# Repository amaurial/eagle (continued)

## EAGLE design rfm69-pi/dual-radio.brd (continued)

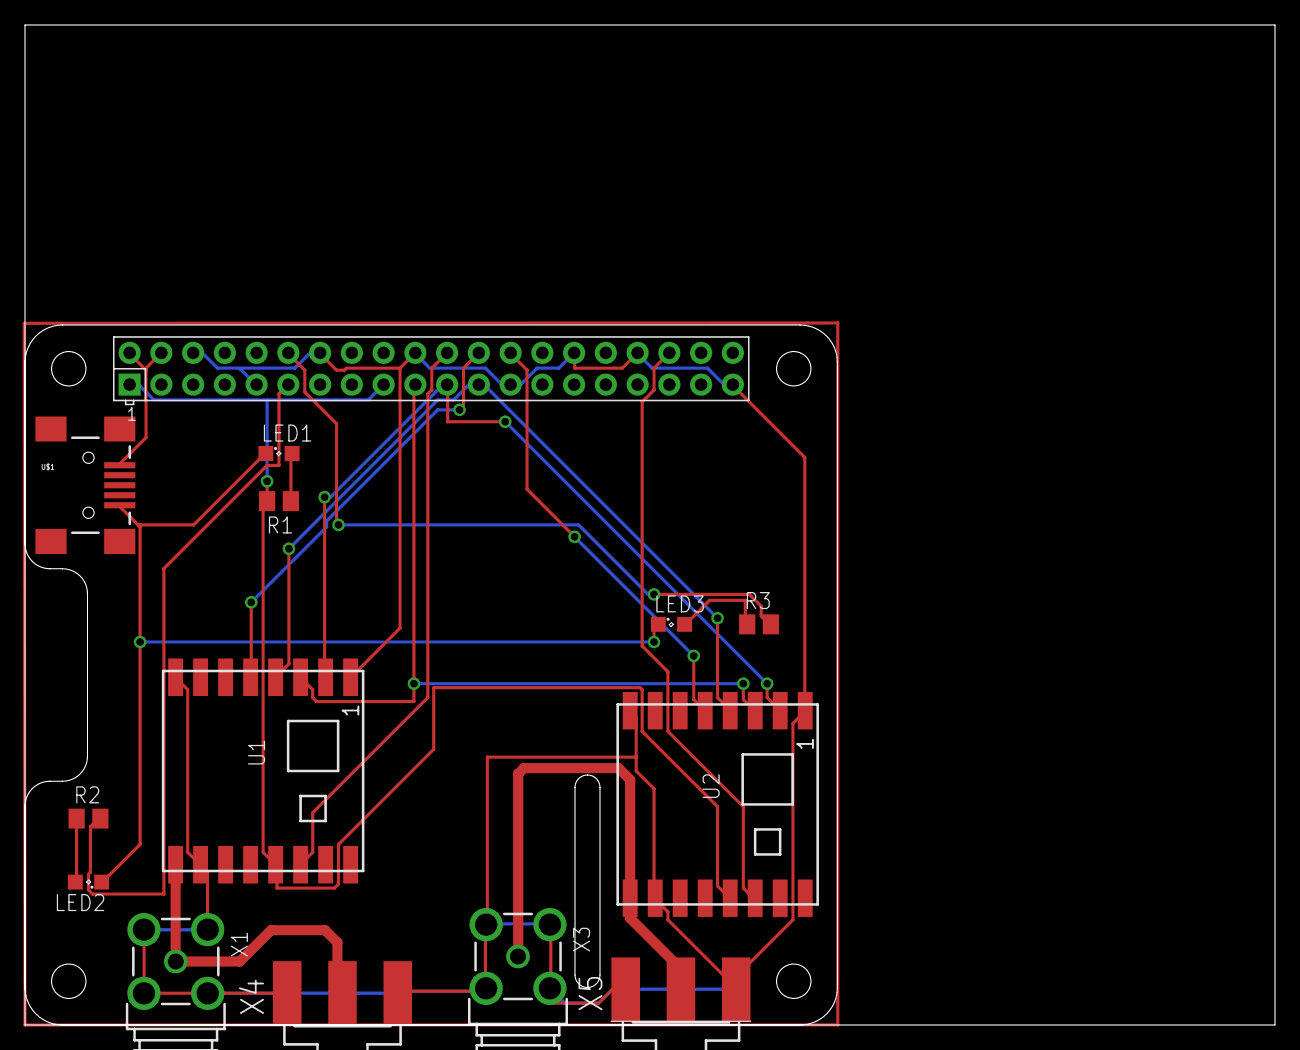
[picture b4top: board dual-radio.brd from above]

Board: 2 copper layers, 100.0 x 80.0 mm, 14 parts (0 on the bottom side), 18 nets.

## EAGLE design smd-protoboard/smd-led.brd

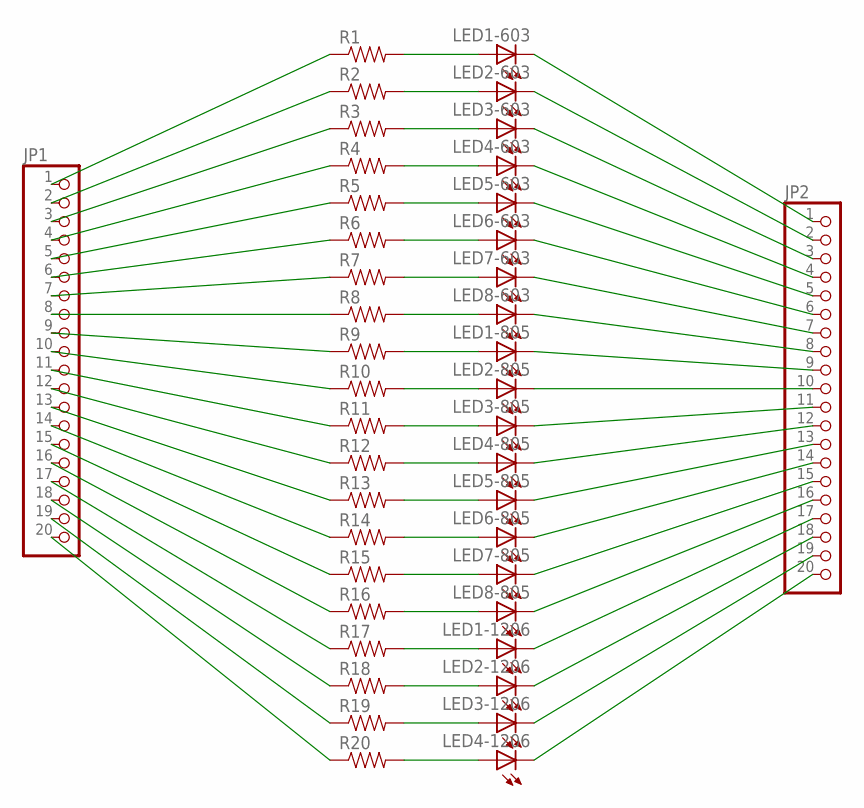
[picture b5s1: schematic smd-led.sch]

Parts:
JP1, JP2: PINHD-1X20; 1X20
LED1-603, LED2-603, LED3-603, LED4-603, LED5-603, LED6-603, LED7-603, LED8-603: LEDSML0603; SML0603
LED1-805, LED2-805, LED3-805, LED4-805, LED5-805, LED6-805, LED7-805, LED8-805: LEDSML0805; SML0805
LED1-1206, LED2-1206, LED3-1206, LED4-1206: LEDSML1206; SML1206
R1, R2, R3, R4, R5, R6, R7, R8, R9, R10, R11, R12, R13, R14, R15, R16, R17, R18, R19, R20: RESISTOR0805-RES; 0805

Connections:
unnamed: JP1.1, R1.1
unnamed: JP1.2, R2.1
unnamed: JP1.3, R3.1
unnamed: JP1.4, R4.1
unnamed: JP1.5, R5.1
unnamed: JP1.6, R6.1
unnamed: JP1.7, R7.1
unnamed: JP1.8, R8.1
unnamed: JP1.9, R9.1
unnamed: JP1.10, R10.1
unnamed: JP1.11, R11.1
unnamed: JP1.12, R12.1
unnamed: JP1.13, R13.1
unnamed: JP1.14, R14.1
unnamed: JP1.15, R15.1
unnamed: JP1.16, R16.1
unnamed: JP1.17, R17.1
unnamed: JP1.18, R18.1
unnamed: JP1.19, R19.1
unnamed: JP1.20, R20.1
unnamed: LED1-603.A, R1.2
unnamed: LED2-603.A, R2.2
unnamed: LED3-603.A, R3.2
unnamed: LED4-603.A, R4.2
unnamed: LED5-603.A, R5.2
unnamed: LED6-603.A, R6.2
unnamed: LED7-603.A, R7.2
unnamed: LED8-603.A, R8.2
unnamed: LED1-805.A, R9.2
unnamed: LED2-805.A, R10.2
unnamed: LED3-805.A, R11.2
unnamed: LED4-805.A, R12.2
unnamed: LED5-805.A, R13.2
unnamed: LED6-805.A, R14.2
unnamed: LED7-805.A, R15.2
unnamed: LED8-805.A, R16.2
unnamed: LED1-1206.A, R17.2
unnamed: LED2-1206.A, R18.2
unnamed: LED3-1206.A, R19.2
unnamed: LED4-1206.A, R20.2
unnamed: JP2.1, LED1-603.C
unnamed: JP2.2, LED2-603.C
unnamed: JP2.3, LED3-603.C
unnamed: JP2.4, LED4-603.C
unnamed: JP2.5, LED5-603.C
unnamed: JP2.6, LED6-603.C
unnamed: JP2.7, LED7-603.C
unnamed: JP2.8, LED8-603.C
unnamed: JP2.9, LED1-805.C
unnamed: JP2.10, LED2-805.C
unnamed: JP2.11, LED3-805.C
unnamed: JP2.12, LED4-805.C
unnamed: JP2.13, LED5-805.C
unnamed: JP2.14, LED6-805.C
unnamed: JP2.15, LED7-805.C
unnamed: JP2.16, LED8-805.C
unnamed: JP2.17, LED1-1206.C
unnamed: JP2.18, LED2-1206.C
unnamed: JP2.19, LED3-1206.C
unnamed: JP2.20, LED4-1206.C

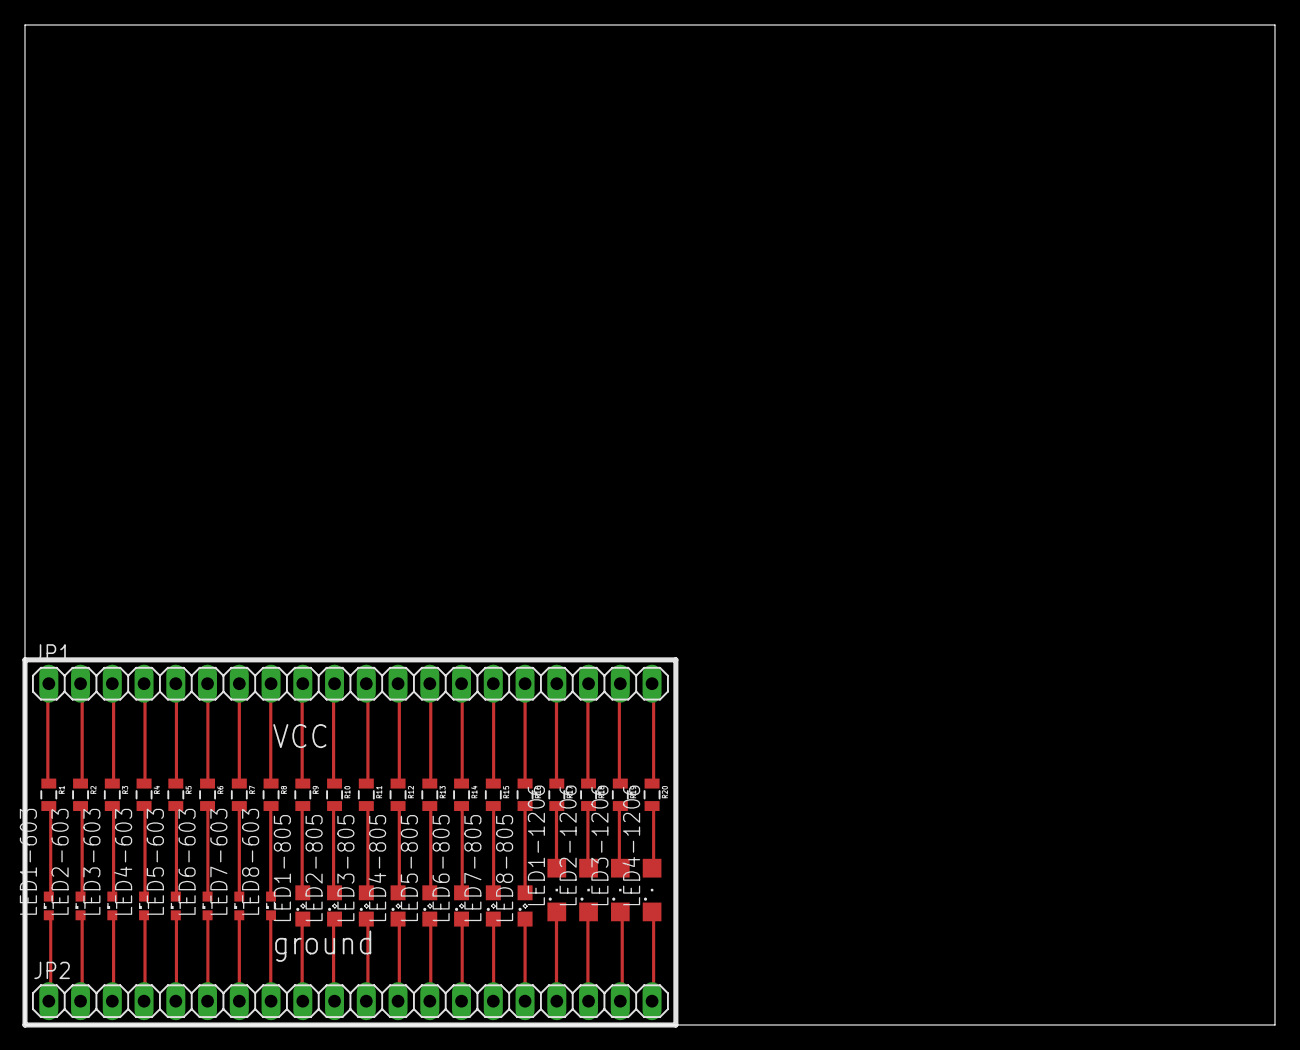
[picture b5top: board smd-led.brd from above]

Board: 2 copper layers, 100.0 x 80.0 mm, 42 parts (0 on the bottom side), 60 nets.

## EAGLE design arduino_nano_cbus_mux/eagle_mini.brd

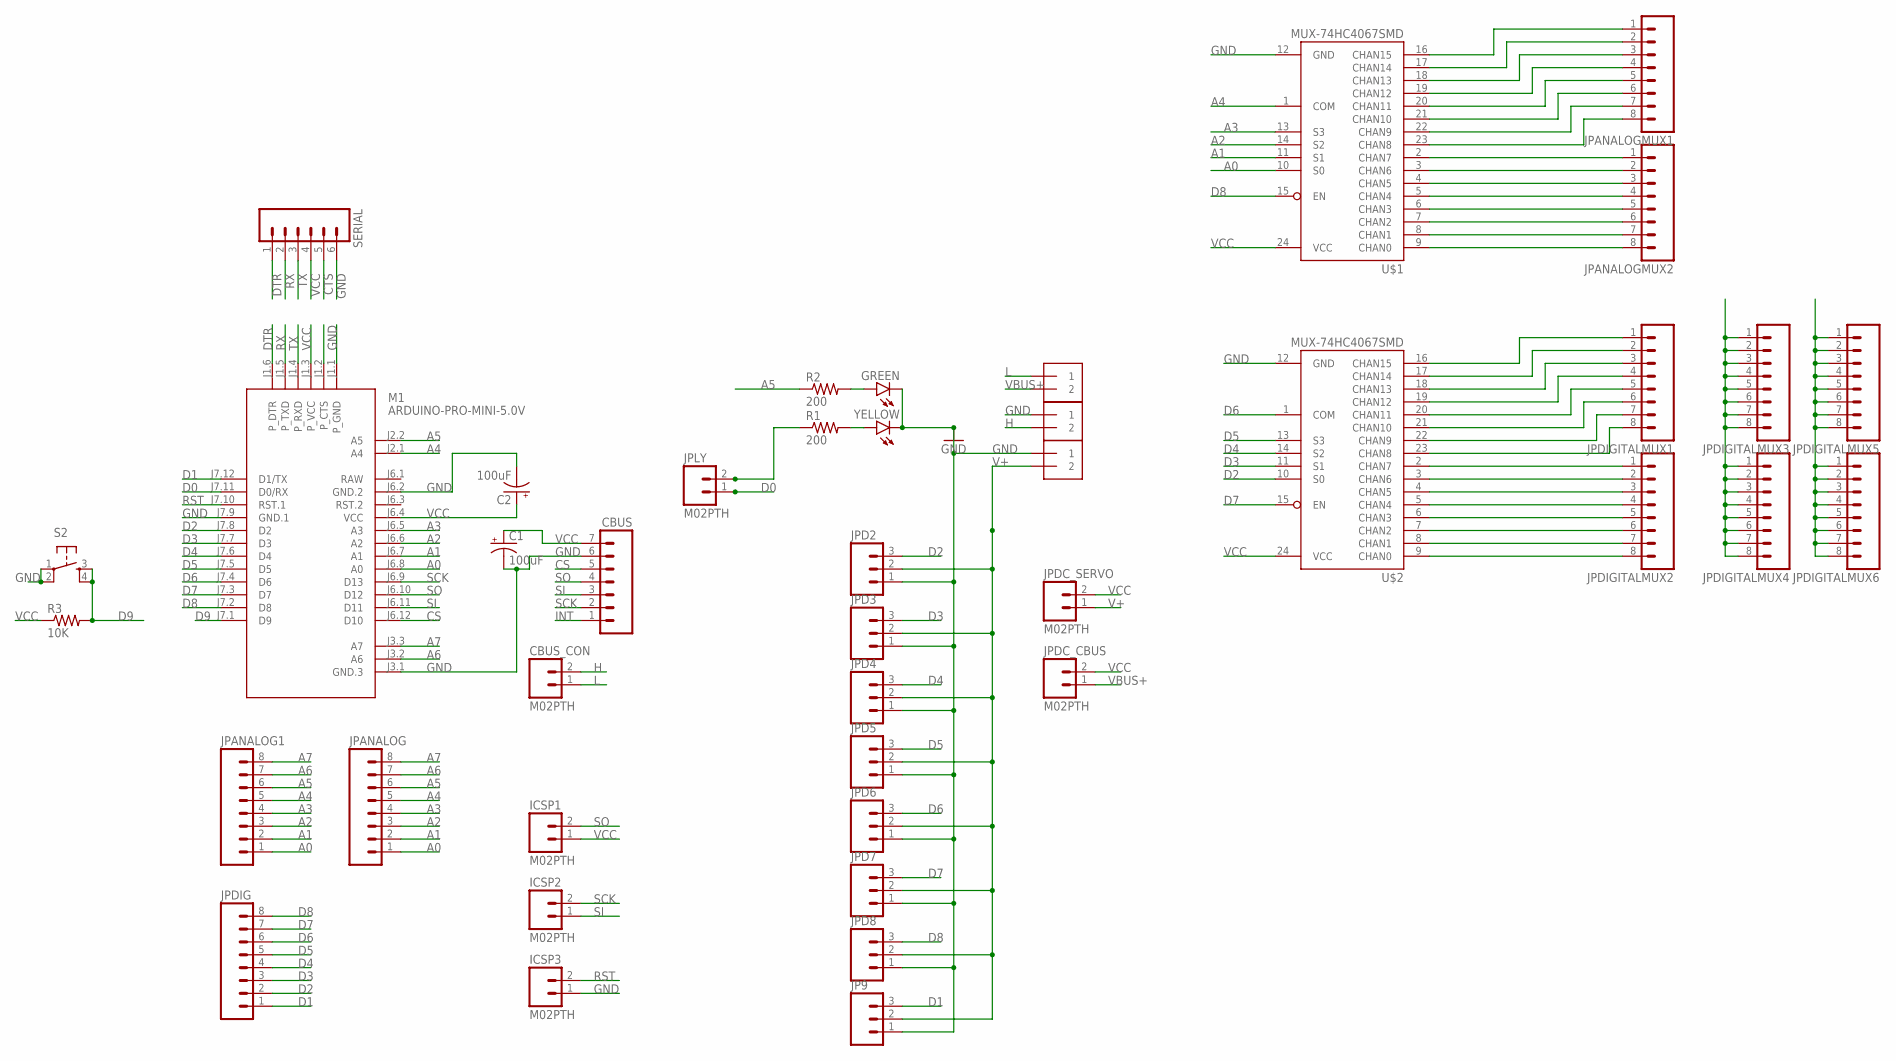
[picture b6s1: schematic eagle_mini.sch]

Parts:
C1, C2: 100uF; E2,5-6
CBUS: M07; 1X07
CBUS_CON: M02PTH; 1X02
EXT_VCC: 1X2-3.5MM
GREEN: LED-3MM-NO_SILK; LED3MM-NS
ICSP1, ICSP2, ICSP3: M02PTH; 1X02
J1, J2: 1X2-3.5MM
JP9: M03PTH; 1X03
JPANALOG, JPANALOG1: M08; 1X08_ROUND
JPANALOGMUX1, JPANALOGMUX2: M08; 1X08_ROUND
JPD2, JPD3, JPD4, JPD5, JPD6, JPD7, JPD8: M03PTH; 1X03
JPDC_CBUS: M02PTH; 1X02
JPDC_SERVO: M02PTH; 1X02
JPDIG: M08; 1X08_ROUND
JPDIGITALMUX1, JPDIGITALMUX2, JPDIGITALMUX3, JPDIGITALMUX4, JPDIGITALMUX5, JPDIGITALMUX6: M08; 1X08_ROUND
JPLY: M02PTH; 1X02
M1: ARDUINO-PRO-MINI-5.0V; ARDUINO-PRO-MINI
R1, R2: 200; AXIAL-0.3
R3: 10K; AXIAL-0.3
S2: TAC_SWITCHPTH; TACTILE-PTH
SERIAL: M06SILK_FEMALE_PTH; 1X06
U$1, U$2: MUX-74HC4067SMD; SSOP24
YELLOW: LED-3MM-NO_SILK; LED3MM-NS

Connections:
6: JPDIGITALMUX2.2, U$2.3 (CHAN6)
A0: JPANALOG.1, JPANALOG1.1, M1.J6.8 (A0), U$1.10 (S0)
A1: JPANALOG.2, JPANALOG1.2, M1.J6.7 (A1), U$1.11 (S1)
A2: JPANALOG.3, JPANALOG1.3, M1.J6.6 (A2), U$1.14 (S2)
A3: JPANALOG.4, JPANALOG1.4, M1.J6.5 (A3), U$1.13 (S3)
A4: JPANALOG.5, JPANALOG1.5, M1.J2.1 (A4), U$1.1 (COM)
A5: JPANALOG.6, JPANALOG1.6, M1.J2.2 (A5), R2.P$1 (1)
A6: JPANALOG.7, JPANALOG1.7, M1.J3.2 (A6)
A7: JPANALOG.8, JPANALOG1.8, M1.J3.3 (A7)
CS: CBUS.5, M1.J6.12 (D10)
CTS: SERIAL.5
D0: JPLY.1, M1.J7.11 (D0/RX)
D1: JP9.3, JPDIG.1, M1.J7.12 (D1/TX)
D2: JPD2.3, JPDIG.2, M1.J7.8 (D2), U$2.10 (S0)
D3: JPD3.3, JPDIG.3, M1.J7.7 (D3), U$2.11 (S1)
D4: JPD4.3, JPDIG.4, M1.J7.6 (D4), U$2.14 (S2)
D5: JPD5.3, JPDIG.5, M1.J7.5 (D5), U$2.13 (S3)
D6: JPD6.3, JPDIG.6, M1.J7.4 (D6), U$2.1 (COM)
D7: JPD7.3, JPDIG.7, M1.J7.3 (D7), U$2.15 (EN)
D8: JPD8.3, JPDIG.8, M1.J7.2 (D8), U$1.15 (EN)
D9: M1.J7.1 (D9), R3.P$2 (2), S2.3, S2.4
DTR: M1.J1.6 (P_DTR), SERIAL.1
GND: C1.-, C2.-, CBUS.6, EXT_VCC.1, GREEN.K (C), ICSP3.1, J1.1, JP9.1, JPD2.1, JPD3.1, JPD4.1, JPD5.1, JPD6.1, JPD7.1, JPD8.1, JPDIGITALMUX3.1, JPDIGITALMUX3.2, JPDIGITALMUX3.3, JPDIGITALMUX3.4, JPDIGITALMUX3.5, JPDIGITALMUX3.6, JPDIGITALMUX3.7, JPDIGITALMUX3.8, JPDIGITALMUX4.1, JPDIGITALMUX4.2, JPDIGITALMUX4.3, JPDIGITALMUX4.4, JPDIGITALMUX4.5, JPDIGITALMUX4.6, JPDIGITALMUX4.7, JPDIGITALMUX4.8, M1.J1.1 (P_GND), M1.J3.1 (GND.3), M1.J6.2 (GND.2), M1.J7.9 (GND.1), S2.1, S2.2, SERIAL.6, U$1.12 (GND), U$2.12 (GND), YELLOW.K (C)
H: CBUS_CON.2, J1.2
INT: CBUS.1
L: CBUS_CON.1, J2.1
MA0: JPANALOGMUX2.8, U$1.9 (CHAN0)
MA1: JPANALOGMUX2.7, U$1.8 (CHAN1)
MA2: JPANALOGMUX2.6, U$1.7 (CHAN2)
MA3: JPANALOGMUX2.5, U$1.6 (CHAN3)
MA4: JPANALOGMUX2.4, U$1.5 (CHAN4)
MA5: JPANALOGMUX2.3, U$1.4 (CHAN5)
MA6: JPANALOGMUX2.2, U$1.3 (CHAN6)
MA7: JPANALOGMUX2.1, U$1.2 (CHAN7)
MA8: JPANALOGMUX1.8, U$1.23 (CHAN8)
MA9: JPANALOGMUX1.7, U$1.22 (CHAN9)
MA10: JPANALOGMUX1.6, U$1.21 (CHAN10)
MA11: JPANALOGMUX1.5, U$1.20 (CHAN11)
MA12: JPANALOGMUX1.4, U$1.19 (CHAN12)
MA13: JPANALOGMUX1.3, U$1.18 (CHAN13)
MA14: JPANALOGMUX1.2, U$1.17 (CHAN14)
MA15: JPANALOGMUX1.1, U$1.16 (CHAN15)
MD0: JPDIGITALMUX2.8, U$2.9 (CHAN0)
MD1: JPDIGITALMUX2.7, U$2.8 (CHAN1)
MD2: JPDIGITALMUX2.6, U$2.7 (CHAN2)
MD3: JPDIGITALMUX2.5, U$2.6 (CHAN3)
MD4: JPDIGITALMUX2.4, U$2.5 (CHAN4)
MD5: JPDIGITALMUX2.3, U$2.4 (CHAN5)
MD7: JPDIGITALMUX2.1, U$2.2 (CHAN7)
MD8: JPDIGITALMUX1.8, U$2.23 (CHAN8)
MD9: JPDIGITALMUX1.7, U$2.22 (CHAN9)
MD10: JPDIGITALMUX1.6, U$2.21 (CHAN10)
MD11: JPDIGITALMUX1.5, U$2.20 (CHAN11)
MD12: JPDIGITALMUX1.4, U$2.19 (CHAN12)
MD13: JPDIGITALMUX1.3, U$2.18 (CHAN13)
MD14: JPDIGITALMUX1.2, U$2.17 (CHAN14)
MD15: JPDIGITALMUX1.1, U$2.16 (CHAN15)
unnamed: GREEN.A, R2.P$2 (2)
unnamed: R1.P$2 (2), YELLOW.A
unnamed: JPLY.2, R1.P$1 (1)
RAW: M1.J6.1 (RAW)
RST: ICSP3.2, M1.J7.10 (RST.1)
RX: M1.J1.5 (P_TXD), SERIAL.2
SCK: CBUS.2, ICSP2.2, M1.J6.9 (D13)
SI: CBUS.3, ICSP2.1, M1.J6.11 (D11)
SO: CBUS.4, ICSP1.2, M1.J6.10 (D12)
TX: M1.J1.4 (P_RXD), SERIAL.3
V+: EXT_VCC.2, JP9.2, JPD2.2, JPD3.2, JPD4.2, JPD5.2, JPD6.2, JPD7.2, JPD8.2, JPDC_SERVO.1, JPDIGITALMUX5.1, JPDIGITALMUX5.2, JPDIGITALMUX5.3, JPDIGITALMUX5.4, JPDIGITALMUX5.5, JPDIGITALMUX5.6, JPDIGITALMUX5.7, JPDIGITALMUX5.8, JPDIGITALMUX6.1, JPDIGITALMUX6.2, JPDIGITALMUX6.3, JPDIGITALMUX6.4, JPDIGITALMUX6.5, JPDIGITALMUX6.6, JPDIGITALMUX6.7, JPDIGITALMUX6.8
VBUS+: J2.2, JPDC_CBUS.1
VCC: C1.+, C2.+, CBUS.7, ICSP1.1, JPDC_CBUS.2, JPDC_SERVO.2, M1.J1.3 (P_VCC), M1.J6.4 (VCC), R3.P$1 (1), SERIAL.4, U$1.24 (VCC), U$2.24 (VCC)

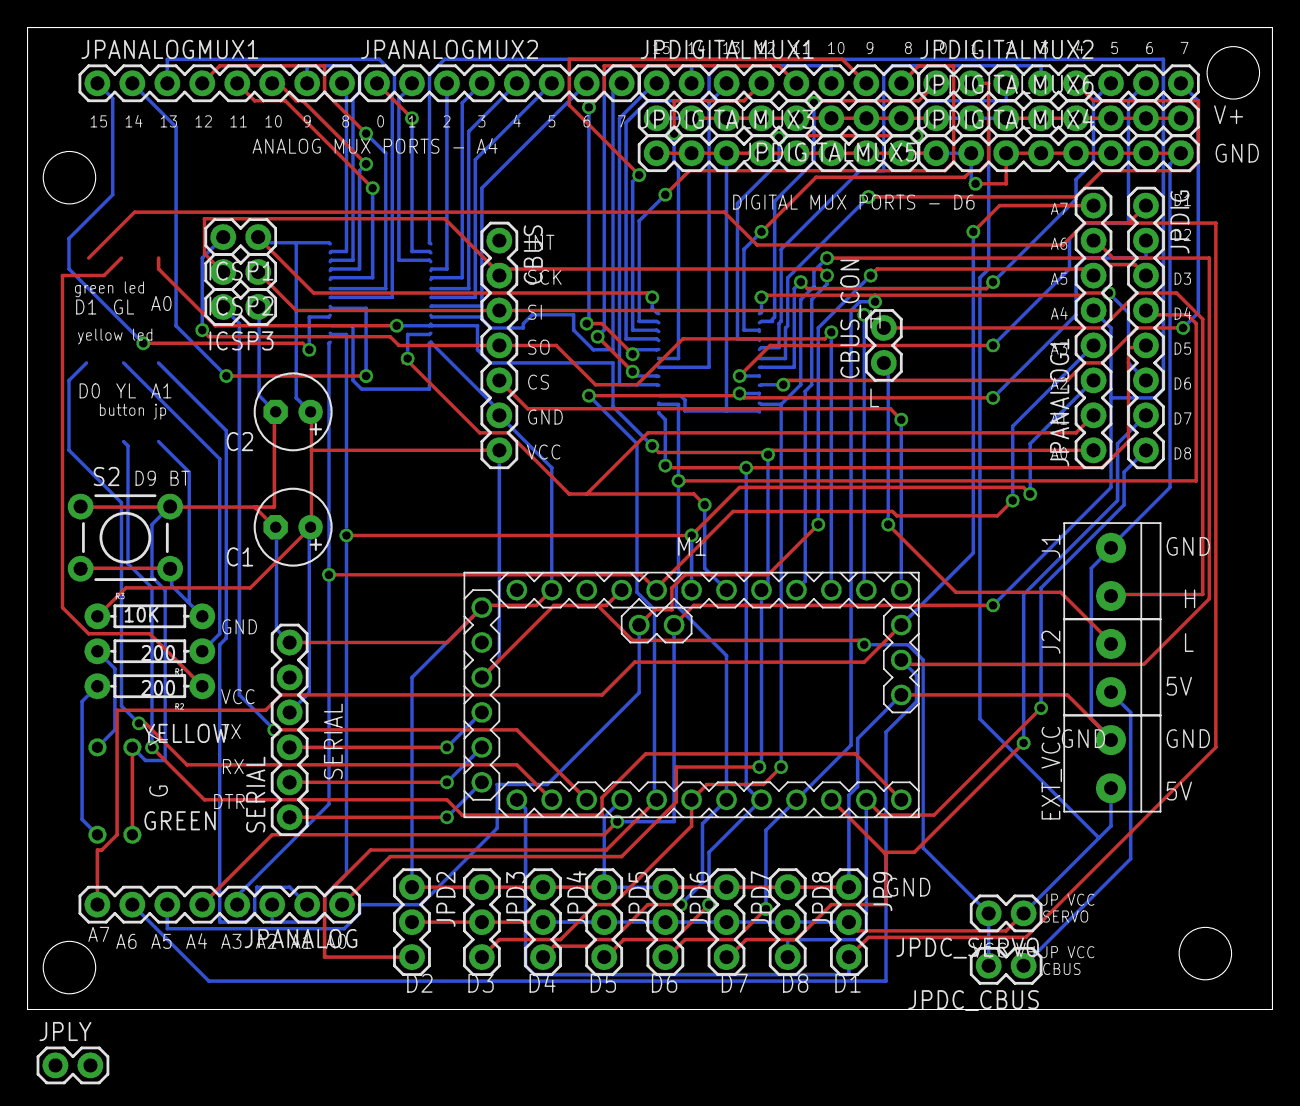
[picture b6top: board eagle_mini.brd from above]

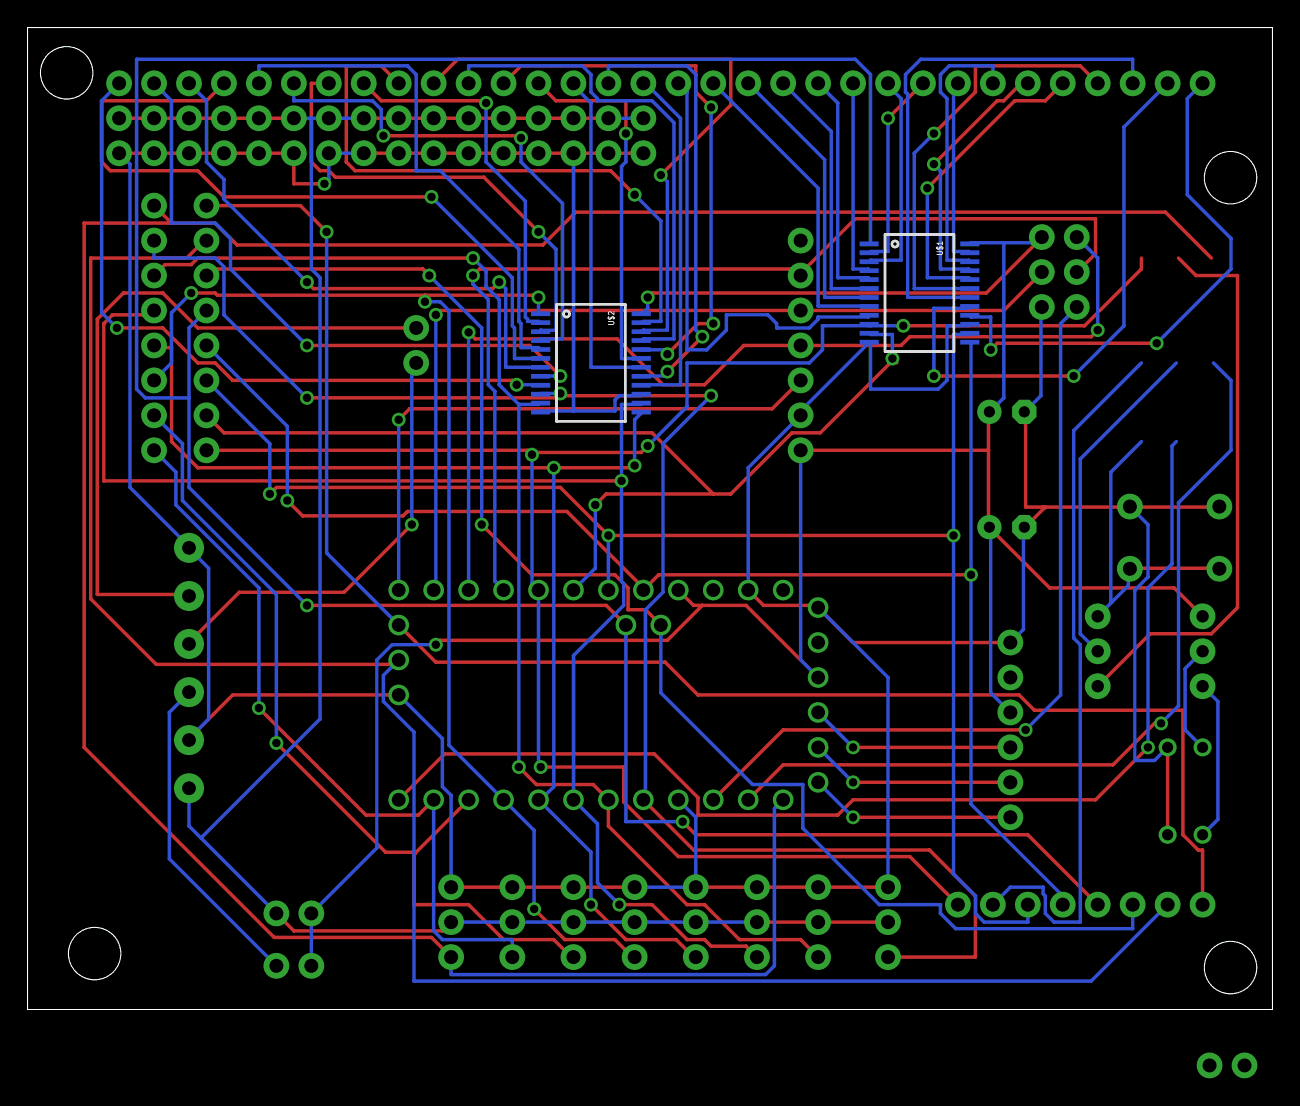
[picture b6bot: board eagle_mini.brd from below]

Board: 2 copper layers, 90.5 x 71.4 mm, 42 parts (2 on the bottom side), 67 nets.

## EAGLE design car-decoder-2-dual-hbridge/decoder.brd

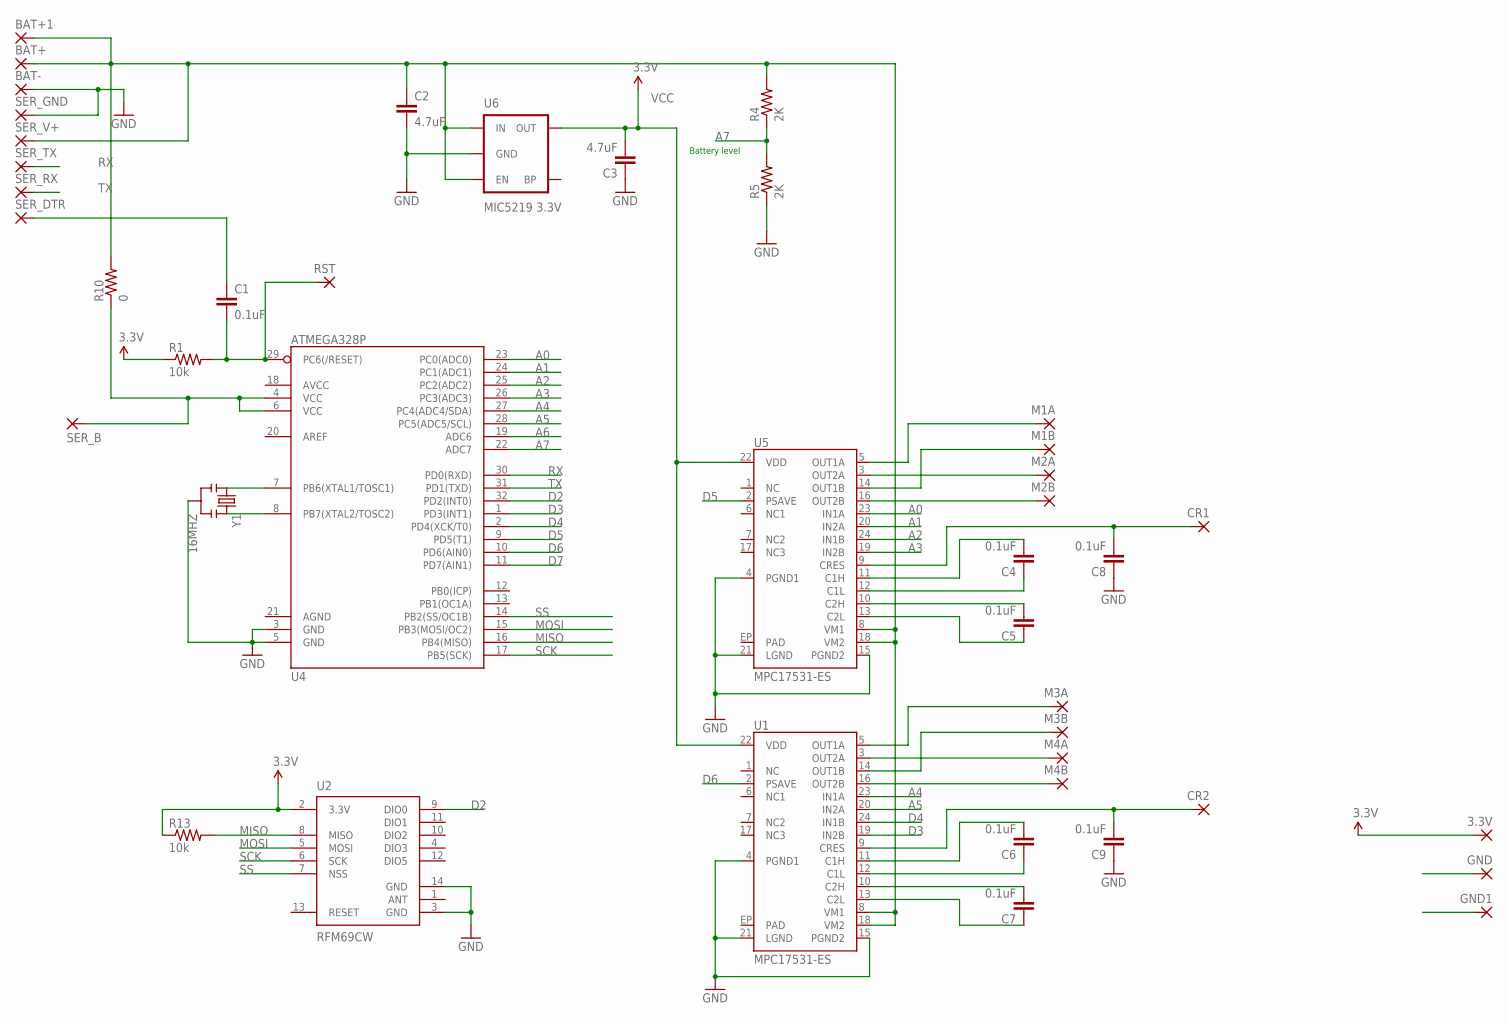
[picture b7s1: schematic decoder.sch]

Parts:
3.3V: SMD2; SMD1,27-2,54
BAT+, BAT+1: SMD2; SMD1,27-2,54
BAT-: SMD2; SMD1,27-2,54
C1, C4, C5, C6, C7, C8, C9: 0.1uF; 0805
C2, C3: 4.7uF; 0805
CR1, CR2: SMD2; SMD1,27-2,54
GND, GND1: SMD2; SMD1,27-2,54
M1A, M1B, M2A, M2B, M3A, M3B, M4A, M4B: SMD2; SMD1,27-2,54
R1, R13: 10k; 0603-RES
R4, R5: 2K; 0603-RES
R10: 0; 0603-RES
RST: SMD2; SMD1,27-2,54
SER_B: SMD2; SMD1,27-2,54
SER_DTR: SMD2; SMD1,27-2,54
SER_GND: SMD2; SMD1,27-2,54
SER_RX: SMD2; SMD1,27-2,54
SER_TX: SMD2; SMD1,27-2,54
SER_V+: SMD2; SMD1,27-2,54
U1, U5: MPC17531-ES; QFN-24_ALT2
U2: RFM69CW; RFM69CW-XXXS2
U4: ATMEGA328P; TQFP32-08
U6: MIC5219 3.3V; SOT23-5
Y1: 16MHZ; RESONATOR-SMD

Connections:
A0: U4.23 (PC0(ADC0)), U5.23 (IN1A)
A1: U4.24 (PC1(ADC1)), U5.20 (IN2A)
A2: U4.25 (PC2(ADC2)), U5.24 (IN1B)
A3: U4.26 (PC3(ADC3)), U5.19 (IN2B)
A4: U1.23 (IN1A), U4.27 (PC4(ADC4/SDA))
A5: U1.20 (IN2A), U4.28 (PC5(ADC5/SCL))
A6: U4.19 (ADC6)
A7: R4.1, R5.2, U4.22 (ADC7)
BAT+: BAT+.1, BAT+1.1, C2.1, R4.2, R10.2, SER_V+.1, U1.8 (VM1), U1.18 (VM2), U5.8 (VM1), U5.18 (VM2), U6.1 (IN), U6.3 (EN)
D2: U2.9 (DIO0), U4.32 (PD2(INT0))
D3: U1.19 (IN2B), U4.1 (PD3(INT1))
D4: U1.24 (IN1B), U4.2 (PD4(XCK/T0))
D5: U4.9 (PD5(T1)), U5.2 (PSAVE)
D6: U1.2 (PSAVE), U4.10 (PD6(AIN0))
D7: U4.11 (PD7(AIN1))
GND: BAT-.1, C2.2, C3.1, C8.1, C9.1, GND.1, GND1.1, R5.1, SER_GND.1, U1.4 (PGND1), U1.15 (PGND2), U1.21 (LGND), U2.3 (GND), U2.14 (GND), U4.3 (GND), U4.5 (GND), U5.4 (PGND1), U5.15 (PGND2), U5.21 (LGND), U6.2 (GND), Y1.2
MISO: R13.2, U2.8 (MISO), U4.16 (PB4(MISO))
MOSI: U2.5 (MOSI), U4.15 (PB3(MOSI/OC2))
unnamed: C4.2, U5.11 (C1H)
unnamed: U4.7 (PB6(XTAL1/TOSC1)), Y1.1
unnamed: C1.1, SER_DTR.1
unnamed: U4.8 (PB7(XTAL2/TOSC2)), Y1.3
unnamed: C1.2, R1.2, RST.1, U4.29 (PC6(/RESET))
unnamed: C4.1, U5.12 (C1L)
unnamed: C5.2, U5.10 (C2H)
unnamed: R10.1, SER_B.1, U4.4 (VCC), U4.6 (VCC)
unnamed: M1A.1, U5.5 (OUT1A)
unnamed: C5.1, U5.13 (C2L)
unnamed: C6.2, U1.11 (C1H)
unnamed: M2A.1, U5.3 (OUT2A)
unnamed: M1B.1, U5.14 (OUT1B)
unnamed: C6.1, U1.12 (C1L)
unnamed: M2B.1, U5.16 (OUT2B)
unnamed: C7.2, U1.10 (C2H)
unnamed: C7.1, U1.13 (C2L)
unnamed: C8.2, CR1.1, U5.9 (CRES)
unnamed: C9.2, CR2.1, U1.9 (CRES)
unnamed: M3A.1, U1.5 (OUT1A)
unnamed: M3B.1, U1.14 (OUT1B)
unnamed: M4A.1, U1.3 (OUT2A)
unnamed: M4B.1, U1.16 (OUT2B)
RX: SER_TX.1, U4.30 (PD0(RXD))
SCK: U2.6 (SCK), U4.17 (PB5(SCK))
SS: U2.7 (NSS), U4.14 (PB2(SS/OC1B))
TX: SER_RX.1, U4.31 (PD1(TXD))
VCC: 3.3V.1, C3.2, R1.1, R13.1, U1.22 (VDD), U2.2 (3.3V), U5.22 (VDD), U6.5 (OUT)

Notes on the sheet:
Battery level

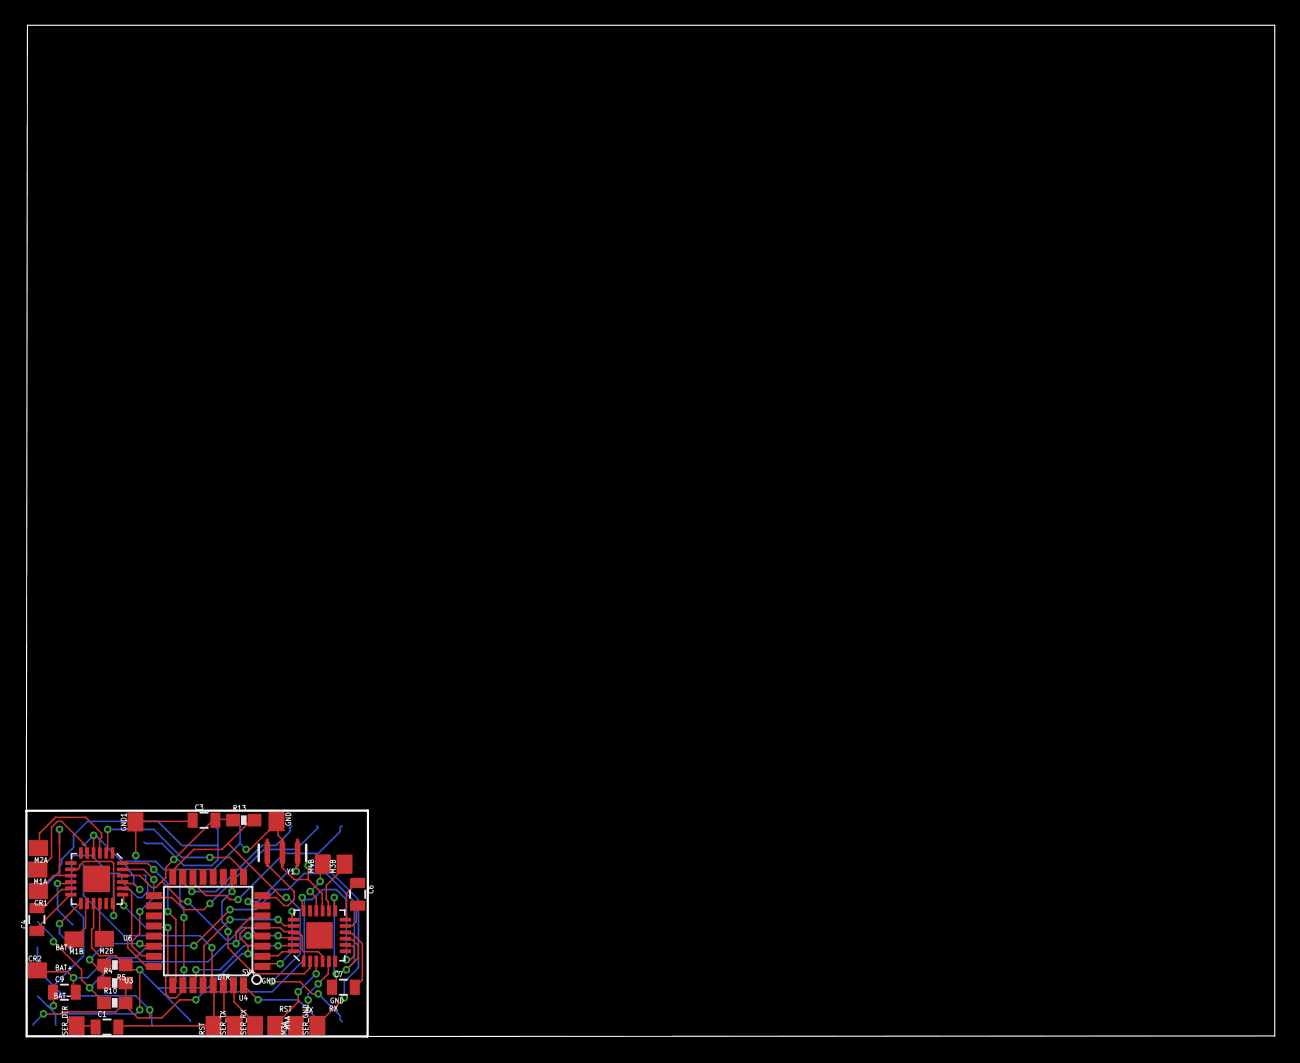
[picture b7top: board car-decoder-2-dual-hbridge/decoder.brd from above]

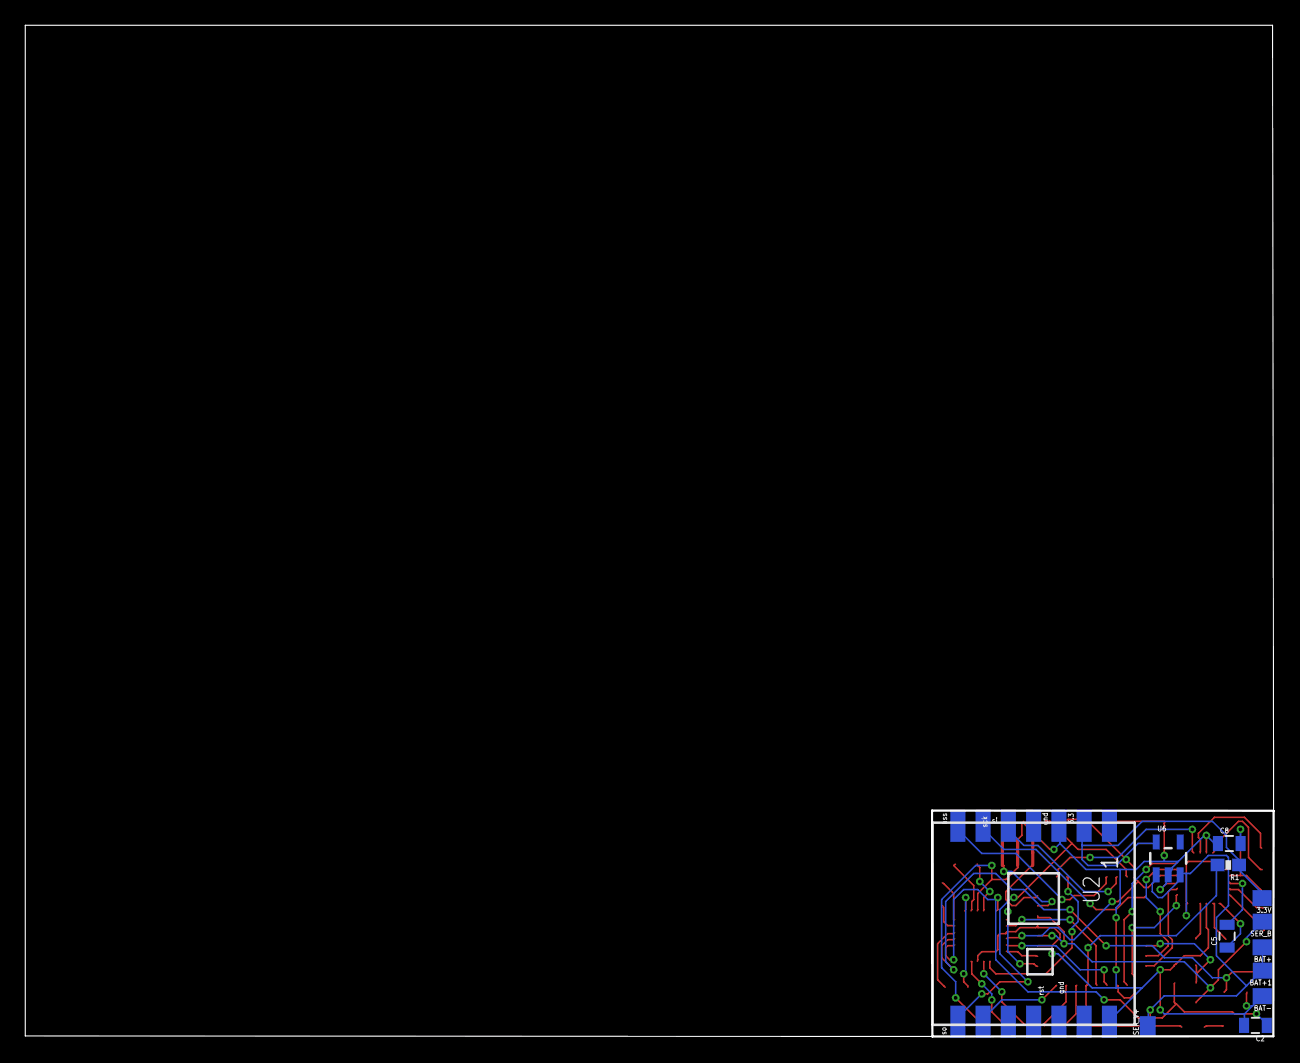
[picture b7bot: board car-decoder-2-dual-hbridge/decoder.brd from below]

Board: 2 copper layers, 98.8 x 80.0 mm, 43 parts (12 on the bottom side), 44 nets.

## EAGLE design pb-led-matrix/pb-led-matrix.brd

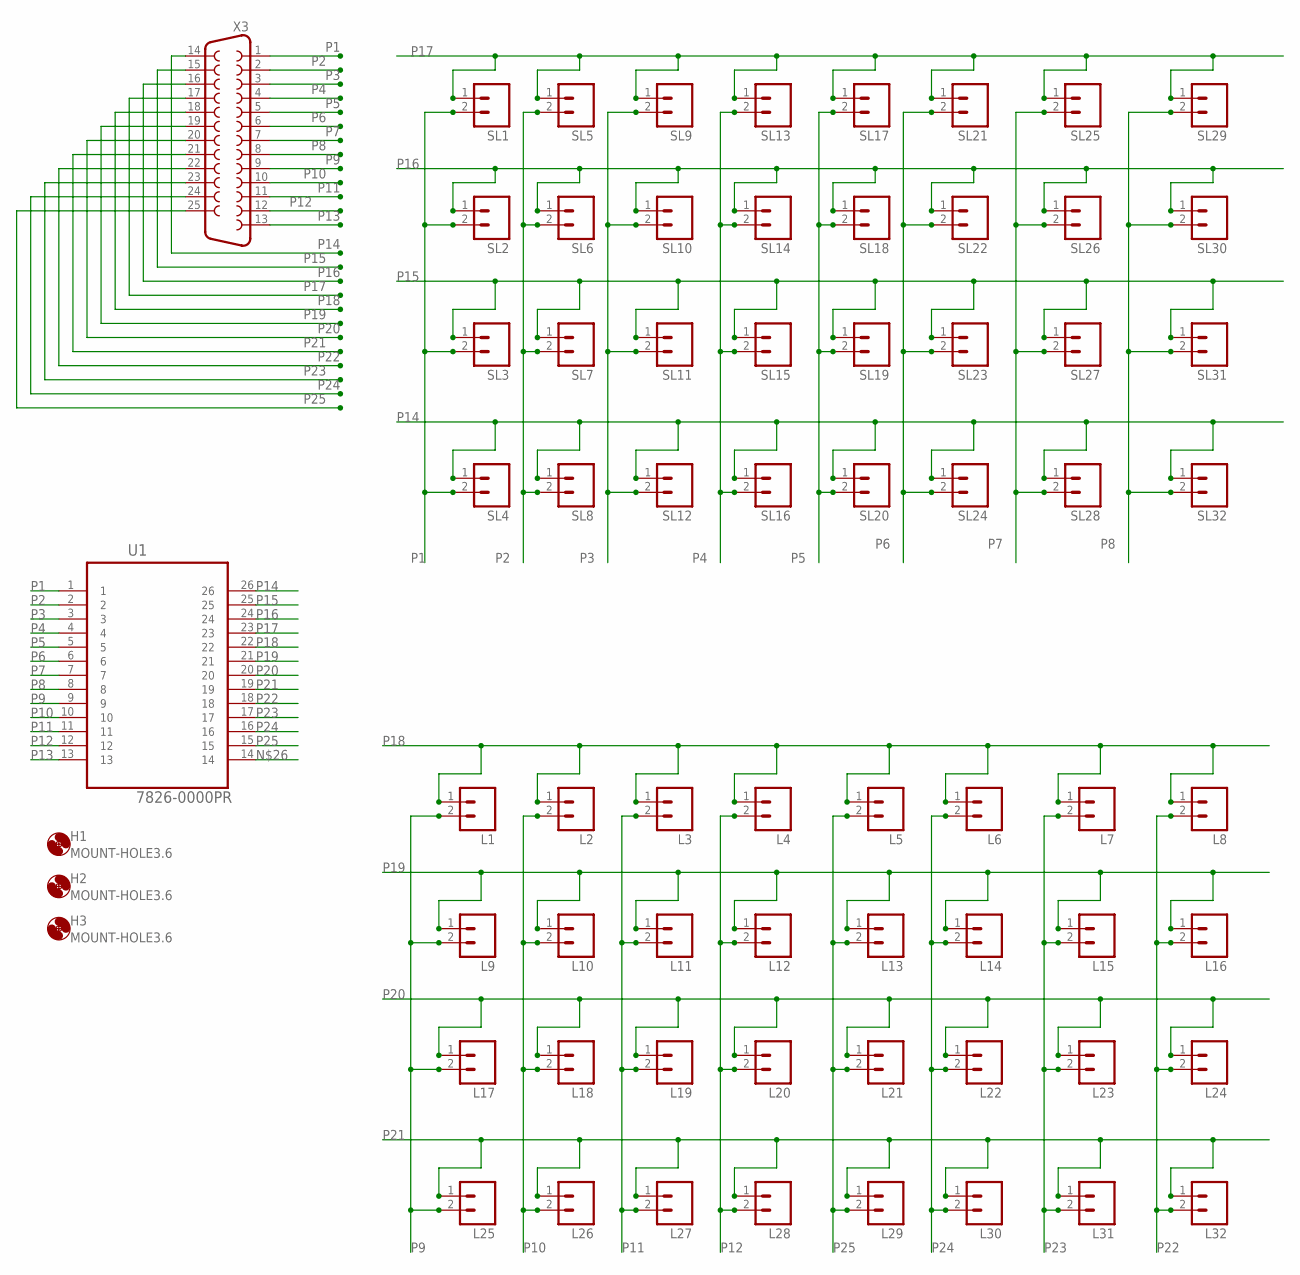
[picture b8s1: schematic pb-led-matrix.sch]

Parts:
H1, H2, H3: MOUNT-HOLE3.6; 3,6
L1, L2, L3, L4, L5, L6, L7, L8, L9, L10, L11, L12, L13, L14, L15, L16, L17, L18, L19, L20, L21, L22, L23, L24, L25, L26, L27, L28, L29, L30, L31, L32: M02; 02P
SL1, SL2, SL3, SL4, SL5, SL6, SL7, SL8, SL9, SL10, SL11, SL12, SL13, SL14, SL15, SL16, SL17, SL18, SL19, SL20, SL21, SL22, SL23, SL24, SL25, SL26, SL27, SL28, SL29, SL30, SL31, SL32: M02; 02P
U1: 7826-0000PR; 3M_7826-0000PR
X3: F25VP

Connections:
P1: SL1.2, SL2.2, SL3.2, SL4.2, U1.1, X3.1
P2: SL5.2, SL6.2, SL7.2, SL8.2, U1.2, X3.2
P3: SL9.2, SL10.2, SL11.2, SL12.2, U1.3, X3.3
P4: SL13.2, SL14.2, SL15.2, SL16.2, U1.4, X3.4
P5: SL17.2, SL18.2, SL19.2, SL20.2, U1.5, X3.5
P6: SL21.2, SL22.2, SL23.2, SL24.2, U1.6, X3.6
P7: SL25.2, SL26.2, SL27.2, SL28.2, U1.7, X3.7
P8: SL29.2, SL30.2, SL31.2, SL32.2, U1.8, X3.8
P9: L1.2, L9.2, L17.2, L25.2, U1.9, X3.9
P10: L2.2, L10.2, L18.2, L26.2, U1.10, X3.10
P11: L3.2, L11.2, L19.2, L27.2, U1.11, X3.11
P12: L4.2, L12.2, L20.2, L28.2, U1.12, X3.12
P13: U1.13, X3.13
P14: SL4.1, SL8.1, SL12.1, SL16.1, SL20.1, SL24.1, SL28.1, SL32.1, U1.26, X3.14
P15: SL3.1, SL7.1, SL11.1, SL15.1, SL19.1, SL23.1, SL27.1, SL31.1, U1.25, X3.15
P16: SL2.1, SL6.1, SL10.1, SL14.1, SL18.1, SL22.1, SL26.1, SL30.1, U1.24, X3.16
P17: SL1.1, SL5.1, SL9.1, SL13.1, SL17.1, SL21.1, SL25.1, SL29.1, U1.23, X3.17
P18: L1.1, L2.1, L3.1, L4.1, L5.1, L6.1, L7.1, L8.1, U1.22, X3.18
P19: L9.1, L10.1, L11.1, L12.1, L13.1, L14.1, L15.1, L16.1, U1.21, X3.19
P20: L17.1, L18.1, L19.1, L20.1, L21.1, L22.1, L23.1, L24.1, U1.20, X3.20
P21: L25.1, L26.1, L27.1, L28.1, L29.1, L30.1, L31.1, L32.1, U1.19, X3.21
P22: L8.2, L16.2, L24.2, L32.2, U1.18, X3.22
P23: L7.2, L15.2, L23.2, L31.2, U1.17, X3.23
P24: L6.2, L14.2, L22.2, L30.2, U1.16, X3.24
P25: L5.2, L13.2, L21.2, L29.2, U1.15, X3.25

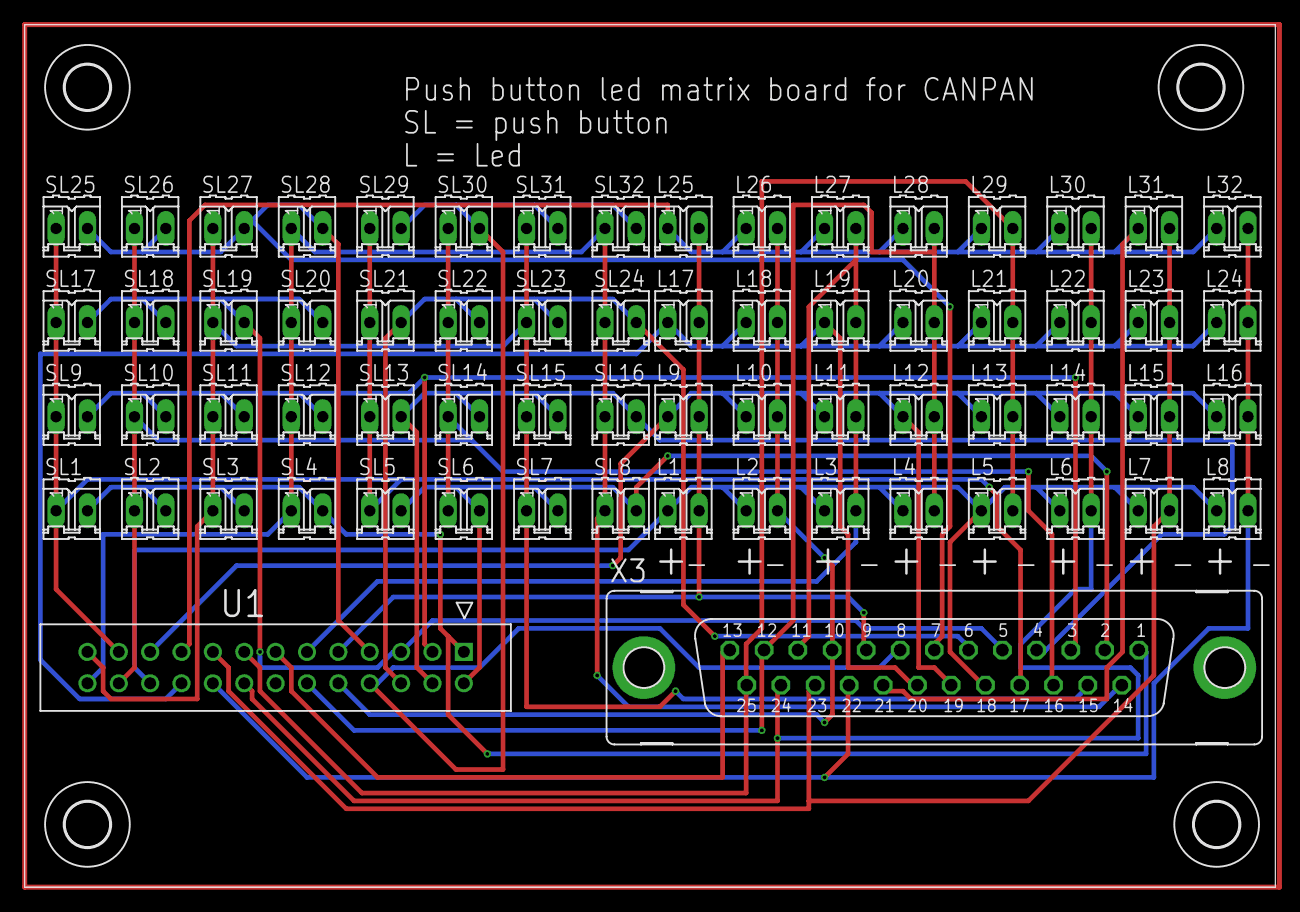
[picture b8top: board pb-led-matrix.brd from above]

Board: 2 copper layers, 101.3 x 69.8 mm, 70 parts (0 on the bottom side), 25 nets.

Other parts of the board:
H4: MOUNT-HOLE3.6; 3,6
